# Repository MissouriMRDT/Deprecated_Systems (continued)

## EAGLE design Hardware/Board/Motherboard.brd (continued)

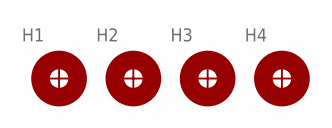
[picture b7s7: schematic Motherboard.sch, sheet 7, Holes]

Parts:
H1, H2, H3, H4: H_MNTHOLE_#4

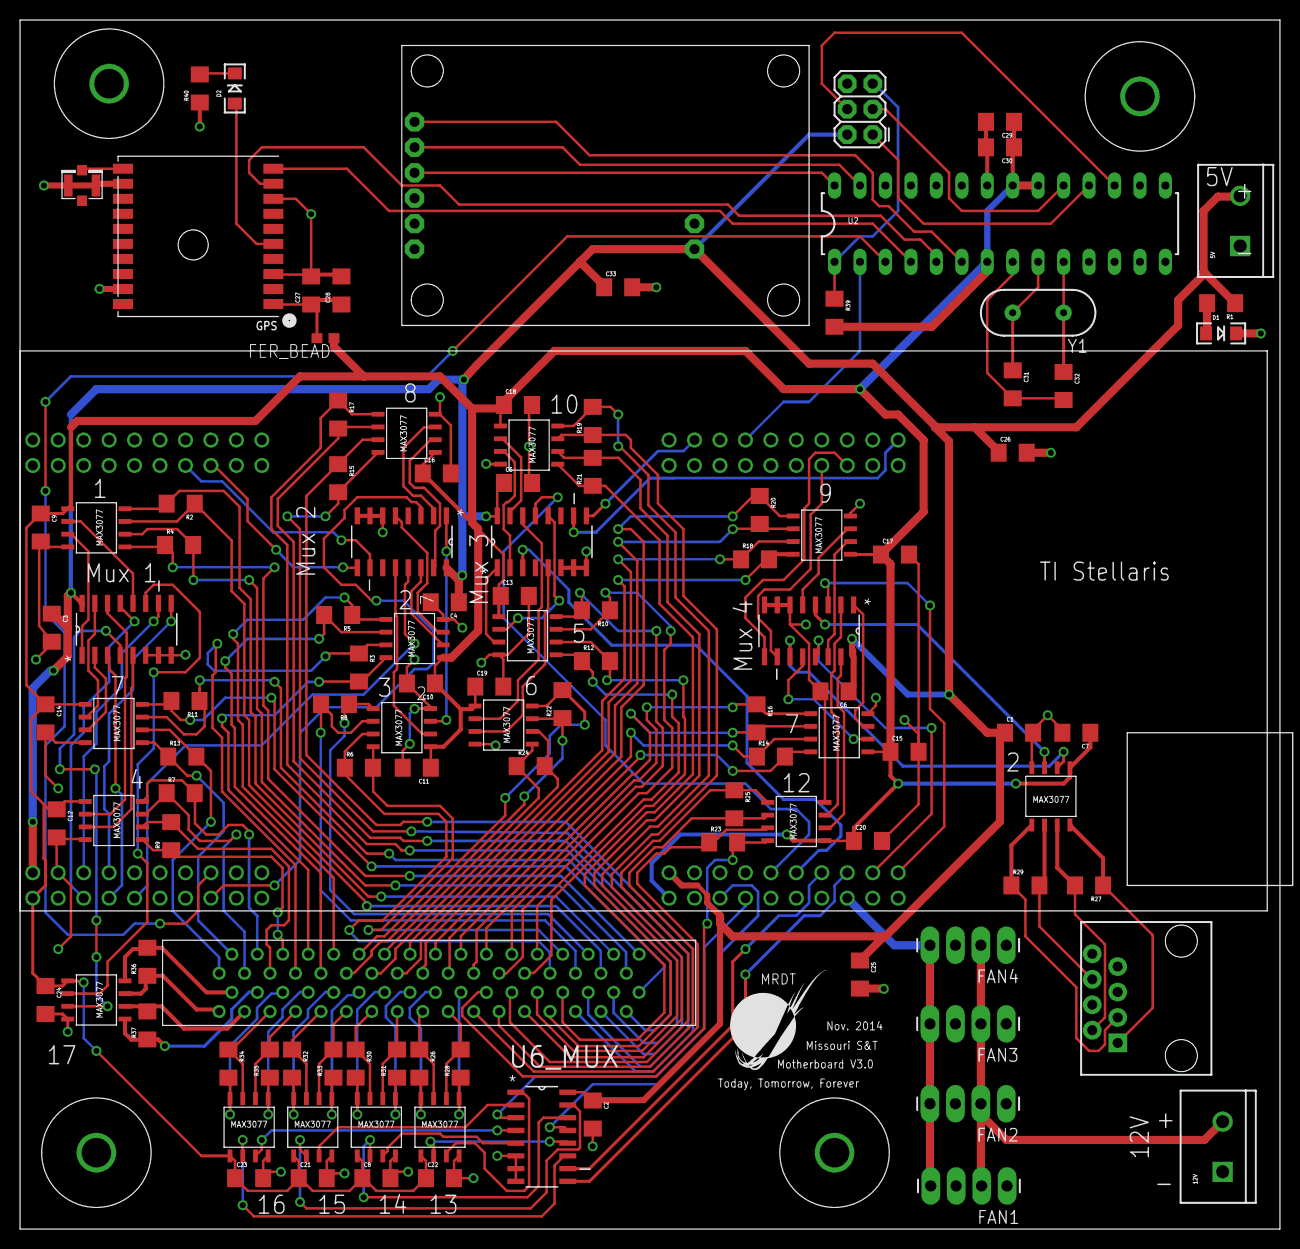
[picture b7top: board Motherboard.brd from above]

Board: 2 copper layers, 125.7 x 120.7 mm, 117 parts (0 on the bottom side), 151 nets.

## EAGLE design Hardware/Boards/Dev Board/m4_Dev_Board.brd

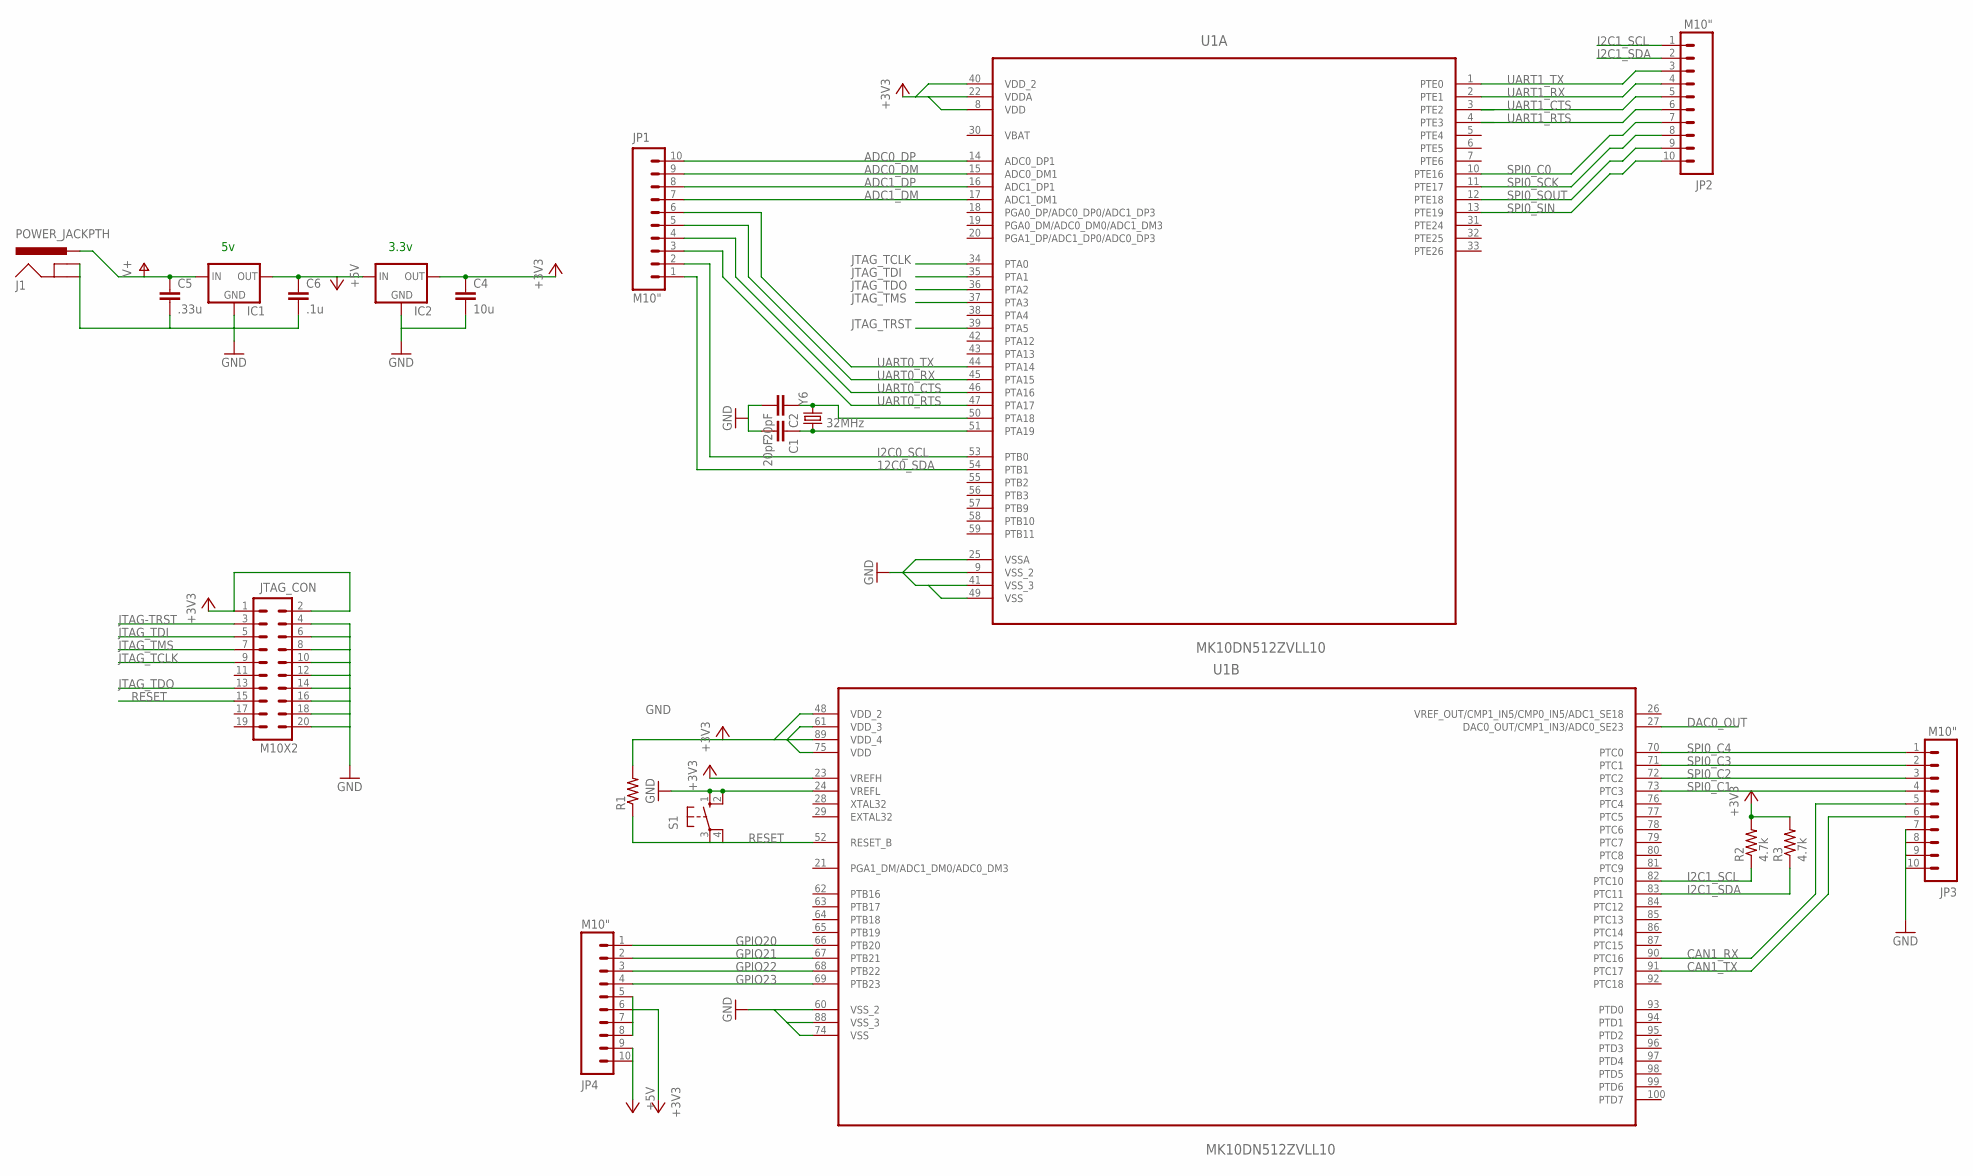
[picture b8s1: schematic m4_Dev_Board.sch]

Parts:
C1, C2: 20pF; CAP-PTH-5MM
C4: 10u; CAP-PTH-5MM
C5: .33u; CAP-PTH-5MM
C6: .1u; CAP-PTH-5MM
IC1, IC2: V_REG_78XXSINK; TO220-IGO
J1: POWER_JACKPTH; POWER_JACK_PTH
JP1, JP2, JP3, JP4: M10"; 1X10
JTAG_CON: M10X2; 2X10
R1: RESISTORPTH-1/4W; AXIAL-0.4
R2, R3: 4.7k; AXIAL-0.4
S1: 10-XX; B3F-10XX
U1: MK10DN512ZVLL10; QFP50P1600X1600X170-100N
Y6: 32MHz; CRYSTAL-SMD-5X3

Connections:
12C0_SDA: JP1.1, U1.54 (PTB1)
+3V3: C4.1, IC2.OUT, JP4.5, JP4.6, JP4.7, JP4.8, JTAG_CON.1, JTAG_CON.2, R1.P$2 (2), R2.P$2 (2), R3.P$2 (2), U1.8 (VDD), U1.22 (VDDA), U1.23 (VREFH), U1.40 (VDD_2), U1.48 (VDD_2), U1.61 (VDD_3), U1.75 (VDD), U1.89 (VDD_4)
+5V: C6.1, IC1.OUT, IC2.IN, JP4.9, JP4.10
ADC0_DM: JP1.9, U1.15 (ADC0_DM1)
ADC0_DP: JP1.10, U1.14 (ADC0_DP1)
ADC1_DM: JP1.7, U1.17 (ADC1_DM1)
ADC1_DP: JP1.8, U1.16 (ADC1_DP1)
CAN1_RX: JP3.5, U1.90 (PTC16)
CAN1_TX: JP3.6, U1.91 (PTC17)
DAC0_OUT: U1.27 (DAC0_OUT/CMP1_IN3/ADC0_SE23)
GND: C1.2, C2.2, C4.2, C5.2, C6.2, IC1.GND, IC2.GND, J1.GND, J1.GNDBREAK, JP3.7, JP3.8, JP3.9, JP3.10, JTAG_CON.4, JTAG_CON.6, JTAG_CON.8, JTAG_CON.10, JTAG_CON.12, JTAG_CON.14, JTAG_CON.16, JTAG_CON.18, JTAG_CON.20, S1.1 (S), S1.2 (S1), U1.9 (VSS_2), U1.24 (VREFL), U1.25 (VSSA), U1.41 (VSS_3), U1.49 (VSS), U1.60 (VSS_2), U1.74 (VSS), U1.88 (VSS_3)
GPIO20: JP4.1, U1.66 (PTB20)
GPIO21: JP4.2, U1.67 (PTB21)
GPIO22: JP4.3, U1.68 (PTB22)
GPIO23: JP4.4, U1.69 (PTB23)
I2C0_SCL: JP1.2, U1.53 (PTB0)
I2C1_SCL: JP2.1, R2.P$1 (1), U1.82 (PTC10)
I2C1_SDA: JP2.2, R3.P$1 (1), U1.83 (PTC11)
JTAG-TRST: JTAG_CON.3
JTAG_TCLK: JTAG_CON.9, U1.34 (PTA0)
JTAG_TDI: JTAG_CON.5, U1.35 (PTA1)
JTAG_TDO: JTAG_CON.13, U1.36 (PTA2)
JTAG_TMS: JTAG_CON.7, U1.37 (PTA3)
JTAG_TRST: U1.39 (PTA5)
unnamed: C2.1, U1.50 (PTA18), Y6.3 (2)
unnamed: C1.1, U1.51 (PTA19), Y6.1
RESET: JTAG_CON.15, R1.P$1 (1), S1.3, S1.4 (P1), U1.52 (RESET_B)
SPI0_C0: JP2.7, U1.10 (PTE16)
SPI0_C1: JP3.4, U1.73 (PTC3)
SPI0_C2: JP3.3, U1.72 (PTC2)
SPI0_C3: JP3.2, U1.71 (PTC1)
SPI0_C4: JP3.1, U1.70 (PTC0)
SPI0_SCK: JP2.8, U1.11 (PTE17)
SPI0_SIN: JP2.10, U1.13 (PTE19)
SPI0_SOUT: JP2.9, U1.12 (PTE18)
UART0_CTS: JP1.4, U1.46 (PTA16)
UART0_RTS: JP1.3, U1.47 (PTA17)
UART0_RX: JP1.5, U1.45 (PTA15)
UART0_TX: JP1.6, U1.44 (PTA14)
UART1_CTS: JP2.5, U1.3 (PTE2)
UART1_RTS: JP2.6, U1.4 (PTE3)
UART1_RX: JP2.4, U1.2 (PTE1)
UART1_TX: JP2.3, U1.1 (PTE0)
V+: C5.1, IC1.IN, J1.PWR
VBAT: U1.30 (VBAT)

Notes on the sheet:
3.3v

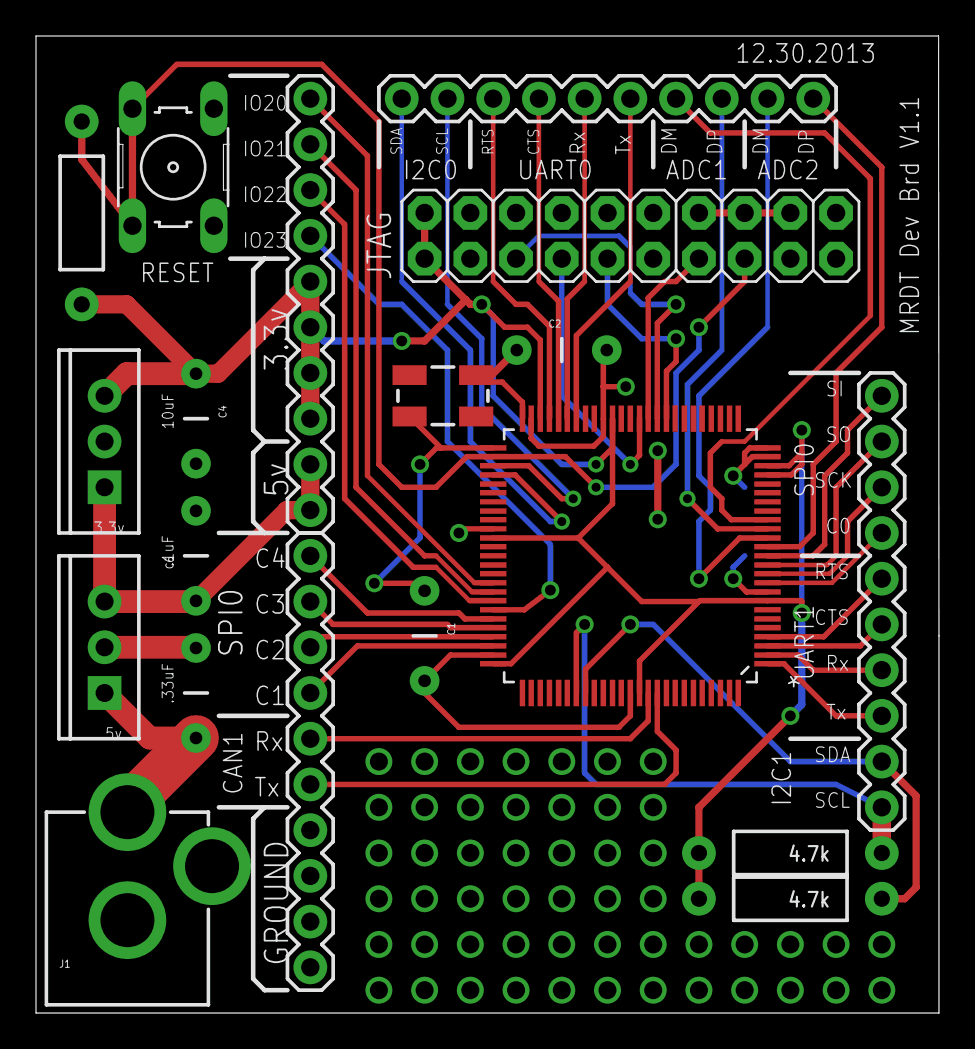
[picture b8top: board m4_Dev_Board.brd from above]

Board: 2 copper layers, 50.2 x 54.3 mm, 19 parts (0 on the bottom side), 41 nets.
